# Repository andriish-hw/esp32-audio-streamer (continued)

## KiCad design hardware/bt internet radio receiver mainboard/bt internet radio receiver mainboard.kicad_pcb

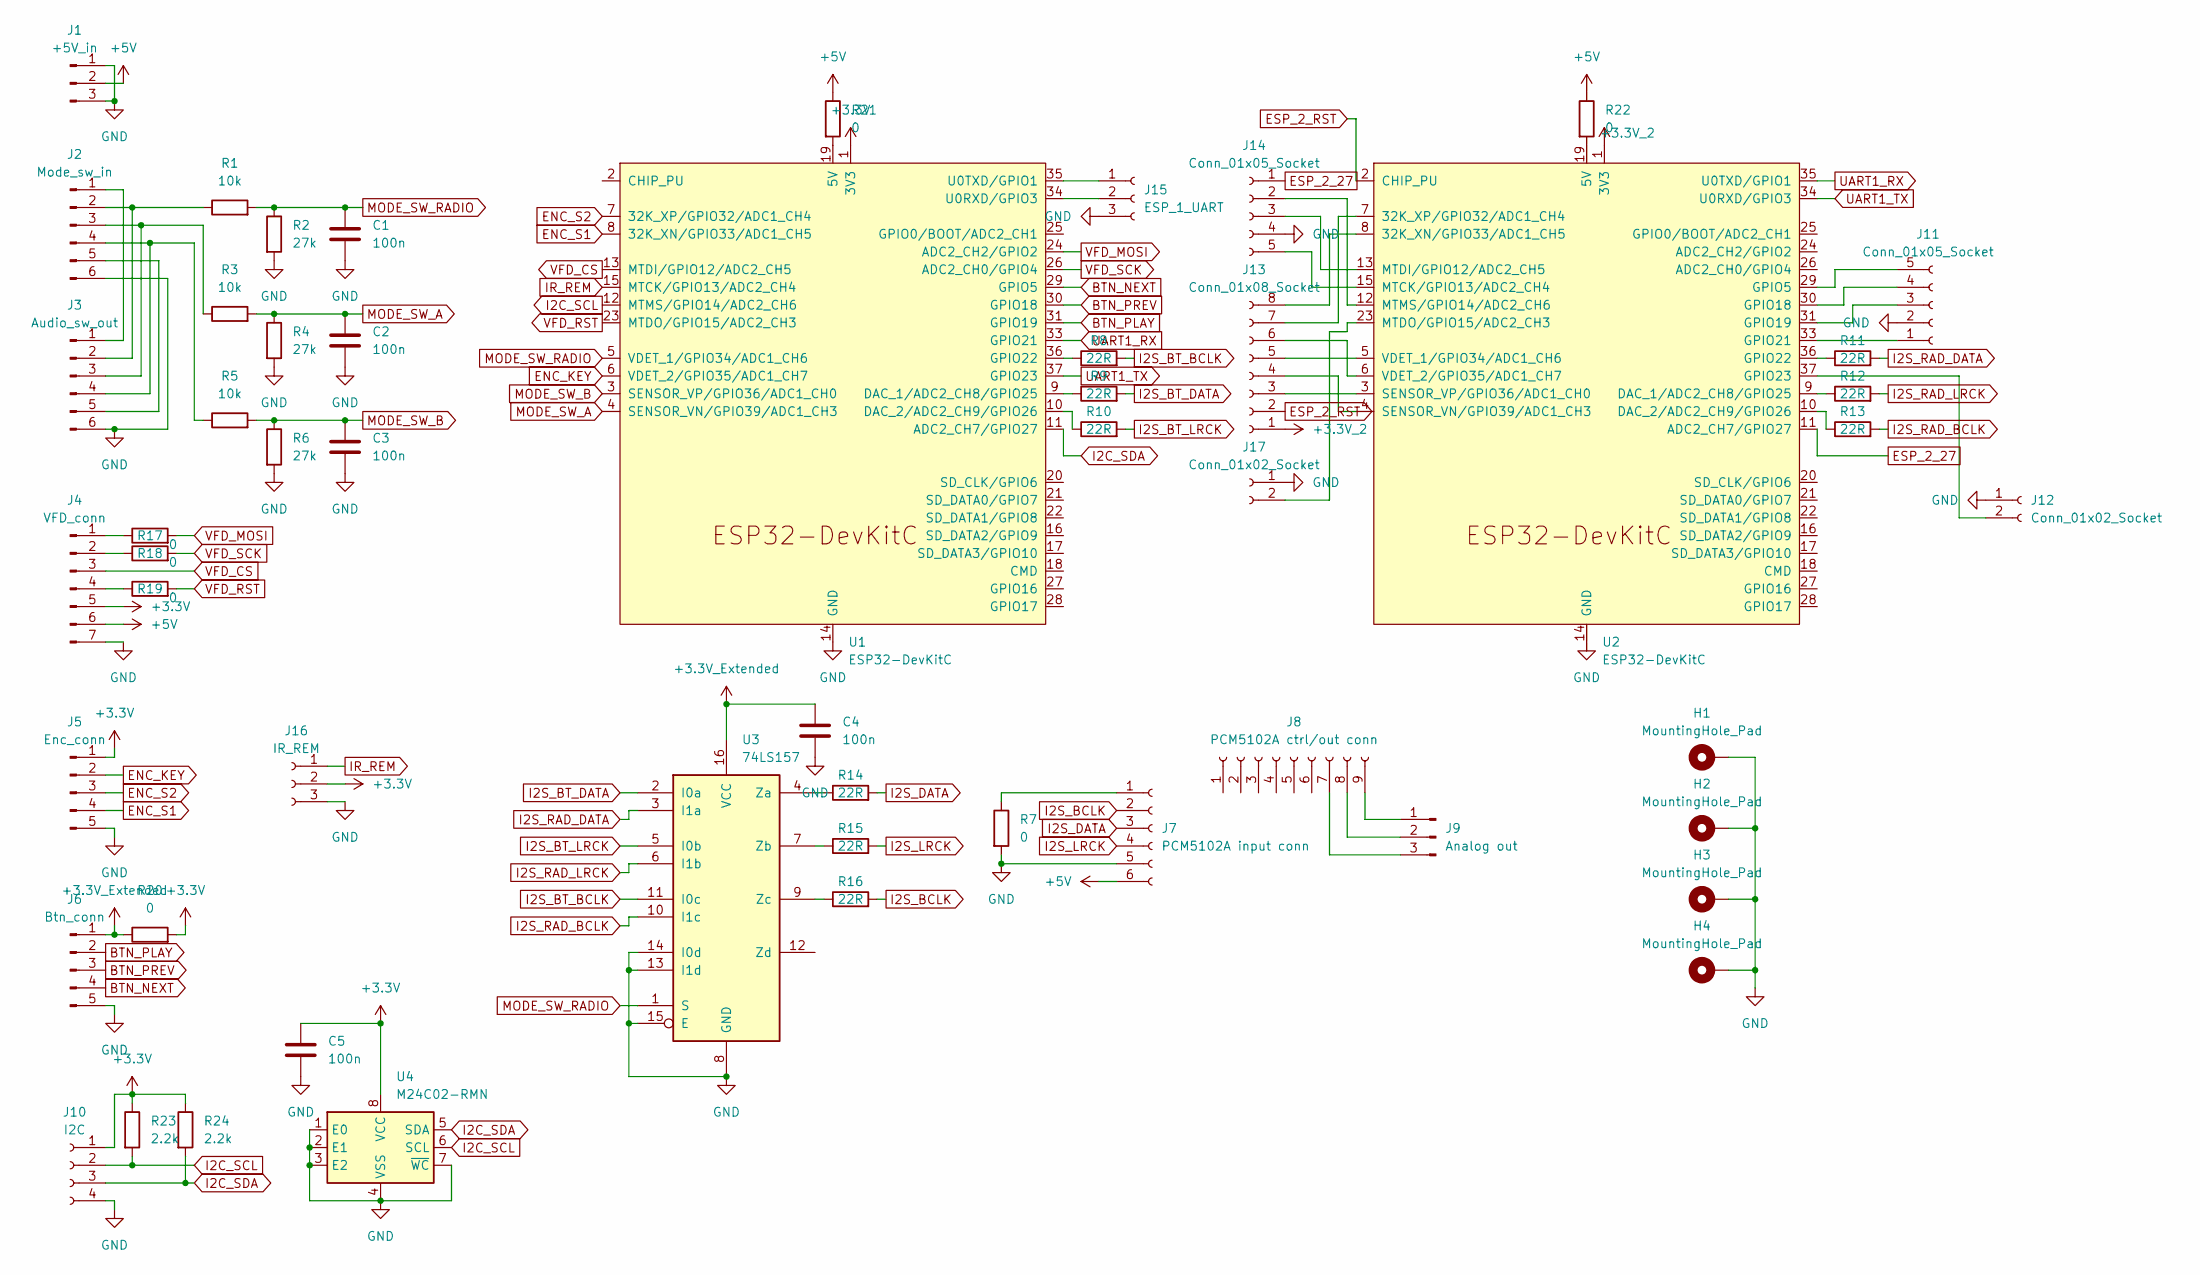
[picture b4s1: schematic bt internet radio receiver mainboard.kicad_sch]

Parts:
C1, C2, C3: 100n; C_Disc_D7.5mm_W5.0mm_P10.00mm
C4, C5: 100n; C_1206_3216Metric_Pad1.33x1.80mm_HandSolder
H1, H2, H3, H4: MountingHole_Pad; MountingHole_3.2mm_M3_DIN965_Pad_TopOnly
J1: +5V_in; PinHeader_1x03_P2.54mm_Vertical
J2: Mode_sw_in; PinHeader_1x06_P2.54mm_Vertical
J3: Audio_sw_out; PinHeader_1x06_P2.54mm_Vertical
J4: VFD_conn; PinHeader_1x07_P2.54mm_Vertical
J5: Enc_conn; PinHeader_1x05_P2.54mm_Vertical
J6: Btn_conn; PinHeader_1x05_P2.54mm_Vertical
J7: PCM5102A input conn; PinSocket_1x06_P2.54mm_Vertical
J8: PCM5102A ctrl/out conn; PinSocket_1x09_P2.54mm_Vertical
J9: Analog out; PinHeader_1x03_P2.54mm_Vertical
J10: I2C; PinSocket_1x04_P2.54mm_Vertical
J11, J14: Conn_01x05_Socket; PinSocket_1x05_P2.54mm_Vertical
J12, J17: Conn_01x02_Socket; PinSocket_1x02_P2.54mm_Vertical
J13: Conn_01x08_Socket; PinSocket_1x08_P2.54mm_Vertical
J15: ESP_1_UART; PinSocket_1x03_P2.54mm_Vertical
J16: IR_REM; PinSocket_1x03_P2.54mm_Vertical
R1, R3, R5: 10k; R_Axial_DIN0207_L6.3mm_D2.5mm_P10.16mm_Horizontal
R2, R4, R6: 27k; R_Axial_DIN0207_L6.3mm_D2.5mm_P10.16mm_Horizontal
R7, R18, R20: 0; R_Axial_DIN0207_L6.3mm_D2.5mm_P10.16mm_Horizontal
R8, R9, R10, R11, R12, R13, R14, R15, R16: 22R; R_Axial_DIN0207_L6.3mm_D2.5mm_P10.16mm_Horizontal
R17, R19: 0; R_Axial_DIN0207_L6.3mm_D2.5mm_P15.24mm_Horizontal
R21, R22: 0; R_Axial_DIN0204_L3.6mm_D1.6mm_P7.62mm_Horizontal
R23: 2.2k; R_Axial_DIN0204_L3.6mm_D1.6mm_P2.54mm_Vertical
R24: 2.2k; R_Axial_DIN0204_L3.6mm_D1.6mm_P5.08mm_Vertical
U1, U2: ESP32-DevKitC
U3: 74LS157; SOIC-16_3.9x9.9mm_P1.27mm
U4: M24C02-RMN; SOIC-8_3.9x4.9mm_P1.27mm

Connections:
+3.3V: C5.1, J4.5, J5.1, J10.1, J16.2, R20.2, R23.1, R24.1, U1.1 (3V3), U4.8 (VCC)
+3.3V_2: J13.1, U2.1 (3V3)
+3.3V_Extended: C4.1, J6.1, R20.1, U3.16 (VCC)
+5V: J1.2, J4.6, J7.6, R21.1, R22.1
BTN_NEXT: J6.4, U1.29 (GPIO5)
BTN_PLAY: J6.2, U1.31 (GPIO19)
BTN_PREV: J6.3, U1.30 (GPIO18)
ENC_KEY: J5.2, U1.6 (VDET_2/GPIO35/ADC1_CH7)
ENC_S1: J5.4, U1.8 (32K_XN/GPIO33/ADC1_CH5)
ENC_S2: J5.3, U1.7 (32K_XP/GPIO32/ADC1_CH4)
ESP_2_27: J14.1, U2.11 (ADC2_CH7/GPIO27)
ESP_2_RST: J13.2, U2.2 (CHIP_PU)
GND: C1.2, C2.2, C3.2, C4.2, C5.2, H1.1, H2.1, H3.1, H4.1, J1.1, J1.3, J2.6, J3.6, J4.7, J5.5, J6.5, J7.5, J10.4, J11.2, J12.1, J14.4, J15.3, J16.3, J17.1, R2.2, R4.2, R6.2, R7.2, U1.14 (GND), U1.32 (GND), U1.38 (GND), U2.14 (GND), U2.32 (GND), U2.38 (GND), U3.8 (GND), U3.13 (I1d), U3.14 (I0d), U3.15 (E), U4.1 (E0), U4.2 (E1), U4.3 (E2), U4.4 (VSS), U4.7 (~WC)
I2C_SCL: J10.2, R23.2, U1.12 (MTMS/GPIO14/ADC2_CH6), U4.6 (SCL)
I2C_SDA: J10.3, R24.2, U1.11 (ADC2_CH7/GPIO27), U4.5 (SDA)
I2S_BCLK: J7.2, R16.2
I2S_BT_BCLK: R8.2, U3.11 (I0c)
I2S_BT_DATA: R9.2, U3.2 (I0a)
I2S_BT_LRCK: R10.2, U3.5 (I0b)
I2S_DATA: J7.3, R14.2
I2S_LRCK: J7.4, R15.2
I2S_RAD_BCLK: R13.2, U3.10 (I1c)
I2S_RAD_DATA: R11.2, U3.3 (I1a)
I2S_RAD_LRCK: R12.2, U3.6 (I1b)
IR_REM: J16.1, U1.15 (MTCK/GPIO13/ADC2_CH4)
MODE_SW_A: C2.1, R3.2, R4.1, U1.4 (SENSOR_VN/GPIO39/ADC1_CH3)
MODE_SW_B: C3.1, R5.2, R6.1, U1.3 (SENSOR_VP/GPIO36/ADC1_CH0)
MODE_SW_RADIO: C1.1, R1.2, R2.1, U1.5 (VDET_1/GPIO34/ADC1_CH6), U3.1 (S)
unnamed: J2.1, J3.1
unnamed: J2.2, J3.2, R1.1
unnamed: J2.3, J3.3, R3.1
unnamed: J2.4, J3.4, R5.1
unnamed: J2.5, J3.5
unnamed: J4.1, R17.1
unnamed: J4.2, R18.1
unnamed: J4.4, R19.1
unnamed: J7.1, R7.1
unnamed: J8.7, J9.3
unnamed: J8.8, J9.2
unnamed: J8.9, J9.1
unnamed: J11.1, U2.33 (GPIO21)
unnamed: J11.3, U2.31 (GPIO19)
unnamed: J11.4, U2.30 (GPIO18)
unnamed: J11.5, U2.29 (GPIO5)
unnamed: J12.2, U2.37 (GPIO23)
unnamed: J13.3, U2.3 (SENSOR_VP/GPIO36/ADC1_CH0)
unnamed: J13.4, U2.4 (SENSOR_VN/GPIO39/ADC1_CH3)
unnamed: J13.5, U2.5 (VDET_1/GPIO34/ADC1_CH6)
unnamed: J13.6, U2.6 (VDET_2/GPIO35/ADC1_CH7)
unnamed: J13.7, U2.7 (32K_XP/GPIO32/ADC1_CH4)
unnamed: J13.8, U2.8 (32K_XN/GPIO33/ADC1_CH5)
unnamed: J14.2, U2.12 (MTMS/GPIO14/ADC2_CH6)
unnamed: J14.3, U2.13 (MTDI/GPIO12/ADC2_CH5)
unnamed: J14.5, U2.15 (MTCK/GPIO13/ADC2_CH4)
unnamed: J15.1, U1.35 (U0TXD/GPIO1)
unnamed: J15.2, U1.34 (U0RXD/GPIO3)
unnamed: J17.2, U2.23 (MTDO/GPIO15/ADC2_CH3)
unnamed: R21.2, U1.19 (5V)
unnamed: R9.1, U1.9 (DAC_1/ADC2_CH8/GPIO25)
unnamed: R10.1, U1.10 (DAC_2/ADC2_CH9/GPIO26)
unnamed: R8.1, U1.36 (GPIO22)
unnamed: R22.2, U2.19 (5V)
unnamed: R12.1, U2.9 (DAC_1/ADC2_CH8/GPIO25)
unnamed: R13.1, U2.10 (DAC_2/ADC2_CH9/GPIO26)
unnamed: R11.1, U2.36 (GPIO22)
unnamed: R14.1, U3.4 (Za)
unnamed: R15.1, U3.7 (Zb)
unnamed: R16.1, U3.9 (Zc)
UART1_RX: U1.33 (GPIO21), U2.35 (U0TXD/GPIO1)
UART1_TX: U1.37 (GPIO23), U2.34 (U0RXD/GPIO3)
VFD_CS: J4.3, U1.13 (MTDI/GPIO12/ADC2_CH5)
VFD_MOSI: R17.2, U1.24 (ADC2_CH2/GPIO2)
VFD_RST: R19.2, U1.23 (MTDO/GPIO15/ADC2_CH3)
VFD_SCK: R18.2, U1.26 (ADC2_CH0/GPIO4)

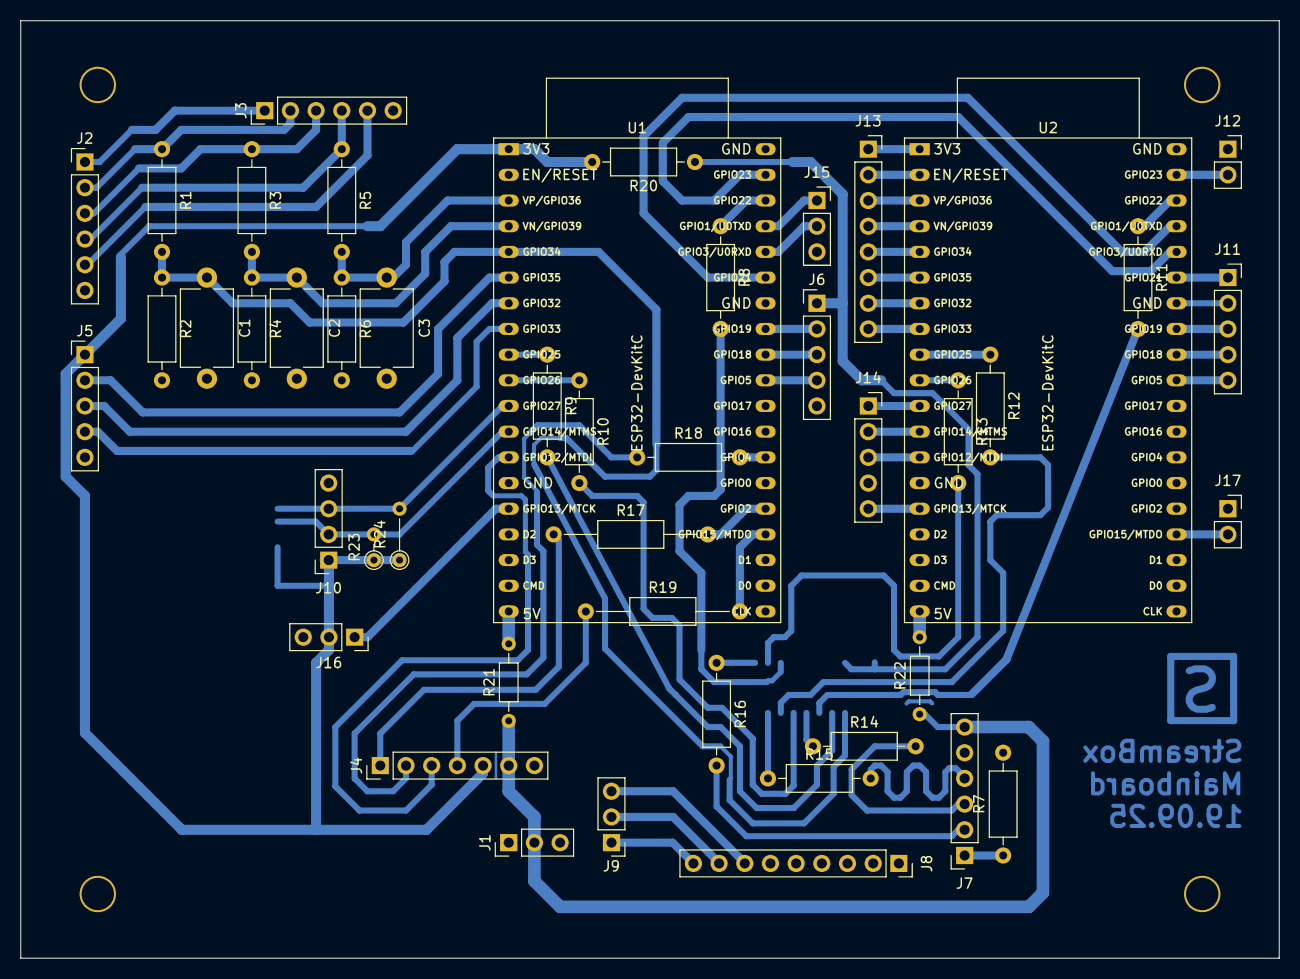
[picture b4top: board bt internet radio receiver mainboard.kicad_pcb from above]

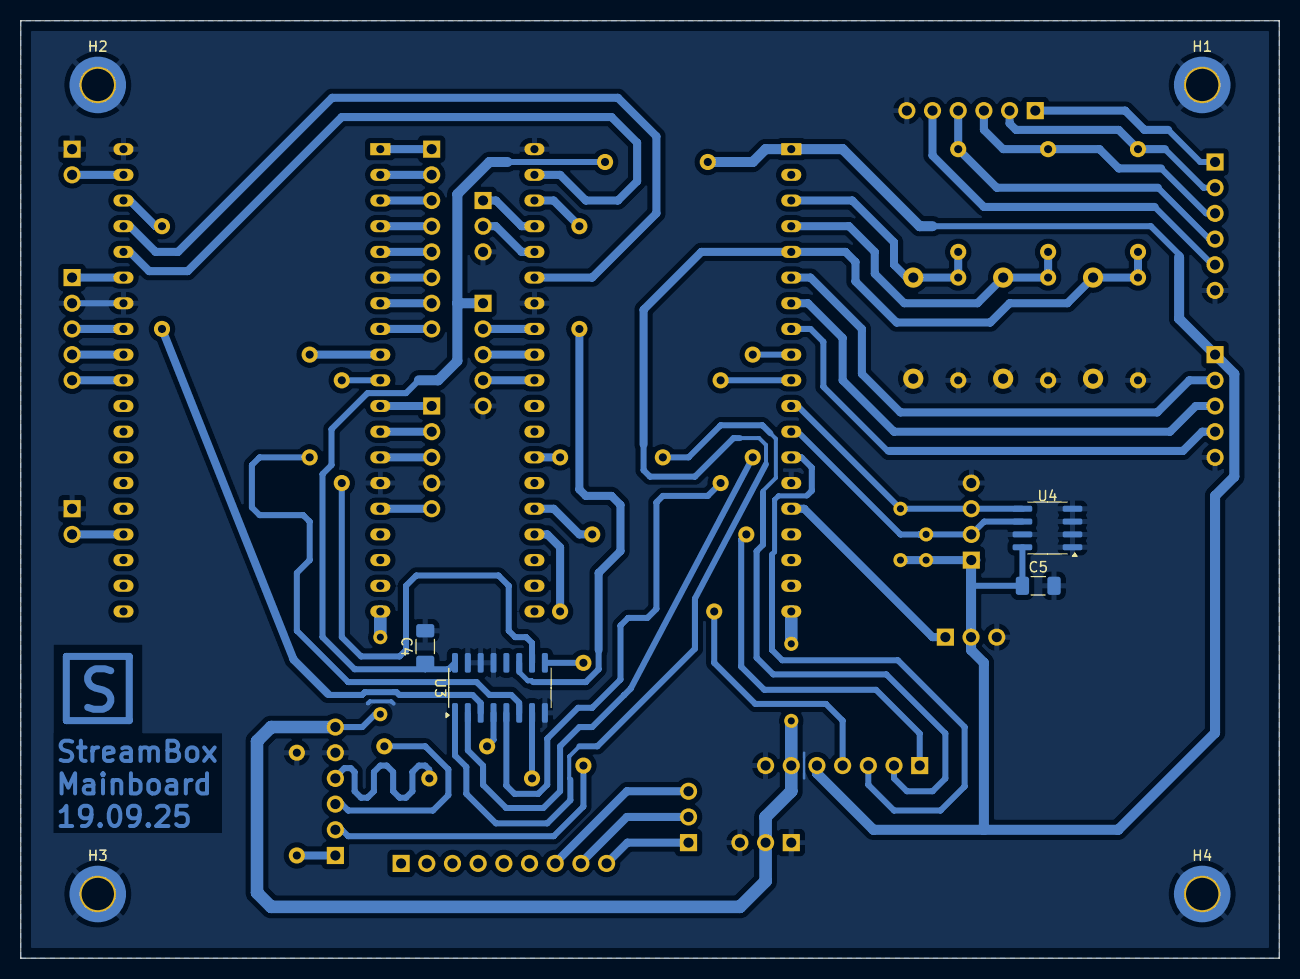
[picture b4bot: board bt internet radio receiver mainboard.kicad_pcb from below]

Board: 2 copper layers, 124.5 x 92.7 mm, 54 parts (8 on the bottom side), 74 nets.

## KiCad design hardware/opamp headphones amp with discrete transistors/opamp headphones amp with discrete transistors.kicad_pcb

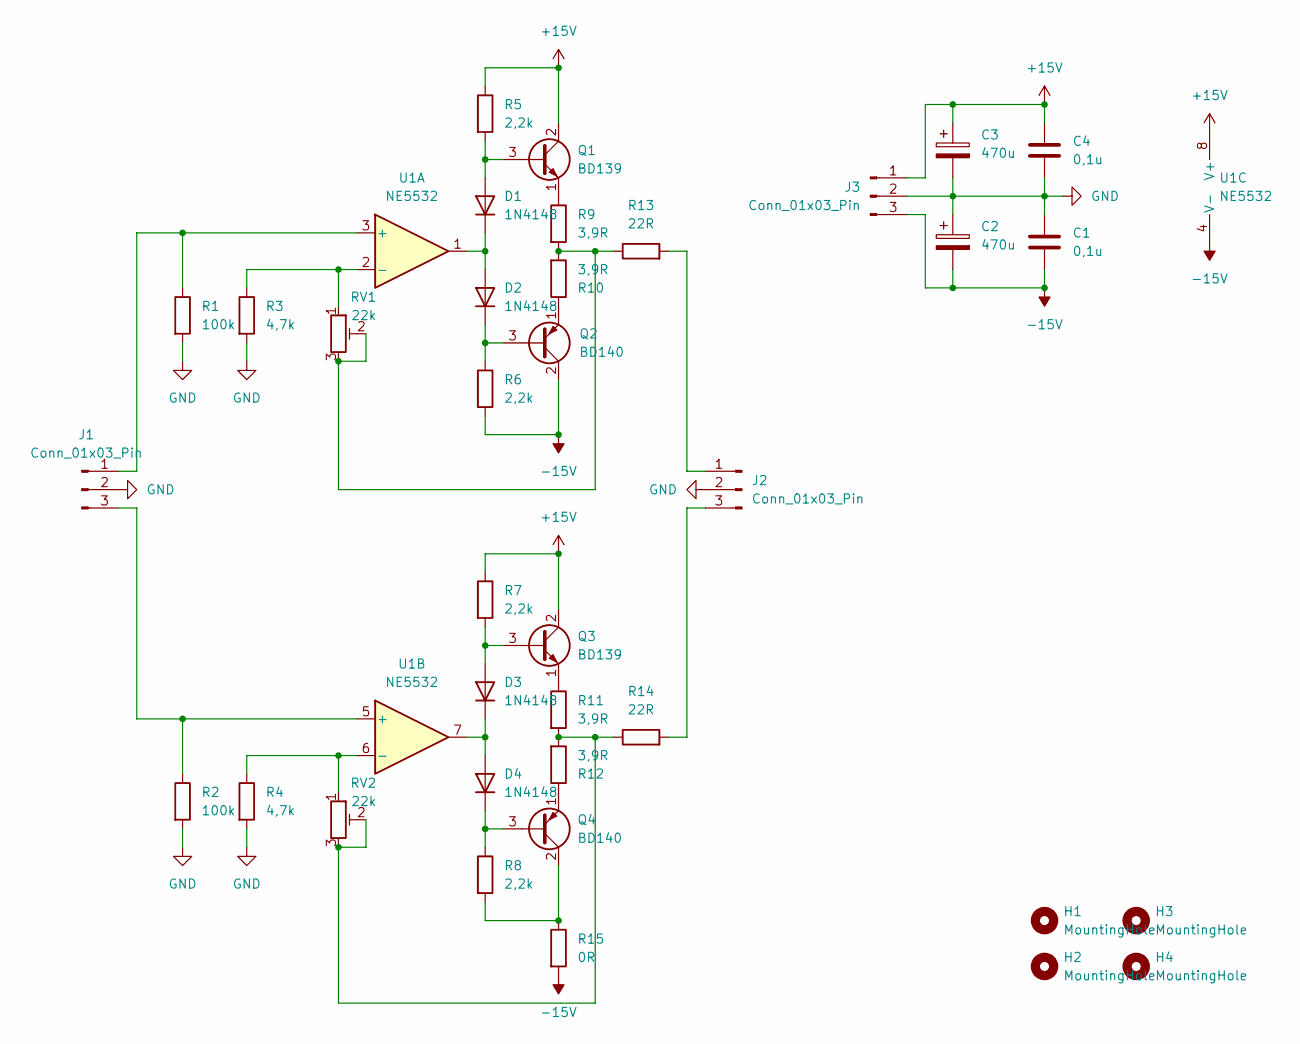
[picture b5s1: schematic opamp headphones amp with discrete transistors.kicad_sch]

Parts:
C1, C4: 0,1u; C_Disc_D5.0mm_W2.5mm_P5.00mm
C2, C3: 470u; CP_Radial_D8.0mm_P2.50mm
D1, D2, D3, D4: 1N4148; D_DO-35_SOD27_P7.62mm_Horizontal
H1, H2, H3, H4: MountingHole; MountingHole_3.2mm_M3_DIN965_Pad
J1, J2, J3: Conn_01x03_Pin; PinHeader_1x03_P2.54mm_Vertical
Q1, Q3: BD139; TO-126-3_Vertical
Q2, Q4: BD140; TO-126-3_Vertical
R1, R2: 100k; R_Axial_DIN0207_L6.3mm_D2.5mm_P10.16mm_Horizontal
R3, R4: 4,7k; R_Axial_DIN0207_L6.3mm_D2.5mm_P10.16mm_Horizontal
R5, R6, R7, R8: 2,2k; R_Axial_DIN0207_L6.3mm_D2.5mm_P10.16mm_Horizontal
R9, R10, R11, R12: 3,9R; R_Axial_DIN0309_L9.0mm_D3.2mm_P5.08mm_Vertical
R13, R14: 22R; R_Axial_DIN0309_L9.0mm_D3.2mm_P5.08mm_Vertical
R15: 0R; R_Axial_DIN0204_L3.6mm_D1.6mm_P7.62mm_Horizontal
RV1, RV2: 22k; Potentiometer_Runtron_RM-065_Vertical
U1: NE5532; DIP-8_W7.62mm_Socket_LongPads

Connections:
+15V: C3.1, C4.1, J3.1, Q1.2 (C), Q3.2 (C), R5.1, R7.1, U1.8 (V+)
-15V: C1.2, C2.2, J3.3, Q2.2 (C), R6.2, R15.2, U1.4 (V-)
GND: C1.1, C2.1, C3.2, C4.2, J1.2, J2.2, J3.2, R1.2, R2.2, R3.2, R4.2
unnamed: D1.2 (A), Q1.3 (B), R5.2
unnamed: D1.1 (K), D2.2 (A), U1.1
unnamed: D2.1 (K), Q2.3 (B), R6.1
unnamed: D3.2 (A), Q3.3 (B), R7.2
unnamed: D3.1 (K), D4.2 (A), U1.7
unnamed: D4.1 (K), Q4.3 (B), R8.1
unnamed: J1.1, R1.1, U1.3 (+)
unnamed: J1.3, R2.1, U1.5 (+)
unnamed: J2.1, R13.2
unnamed: J2.3, R14.2
unnamed: Q1.1 (E), R9.1
unnamed: Q2.1 (E), R10.1
unnamed: Q3.1 (E), R11.1
unnamed: Q4.2 (C), R8.2, R15.1
unnamed: Q4.1 (E), R12.1
unnamed: R9.2, R10.2, R13.1, RV1.2, RV1.3
unnamed: R11.2, R12.2, R14.1, RV2.2, RV2.3
unnamed: R3.1, RV1.1, U1.2 (-)
unnamed: R4.1, RV2.1, U1.6 (-)

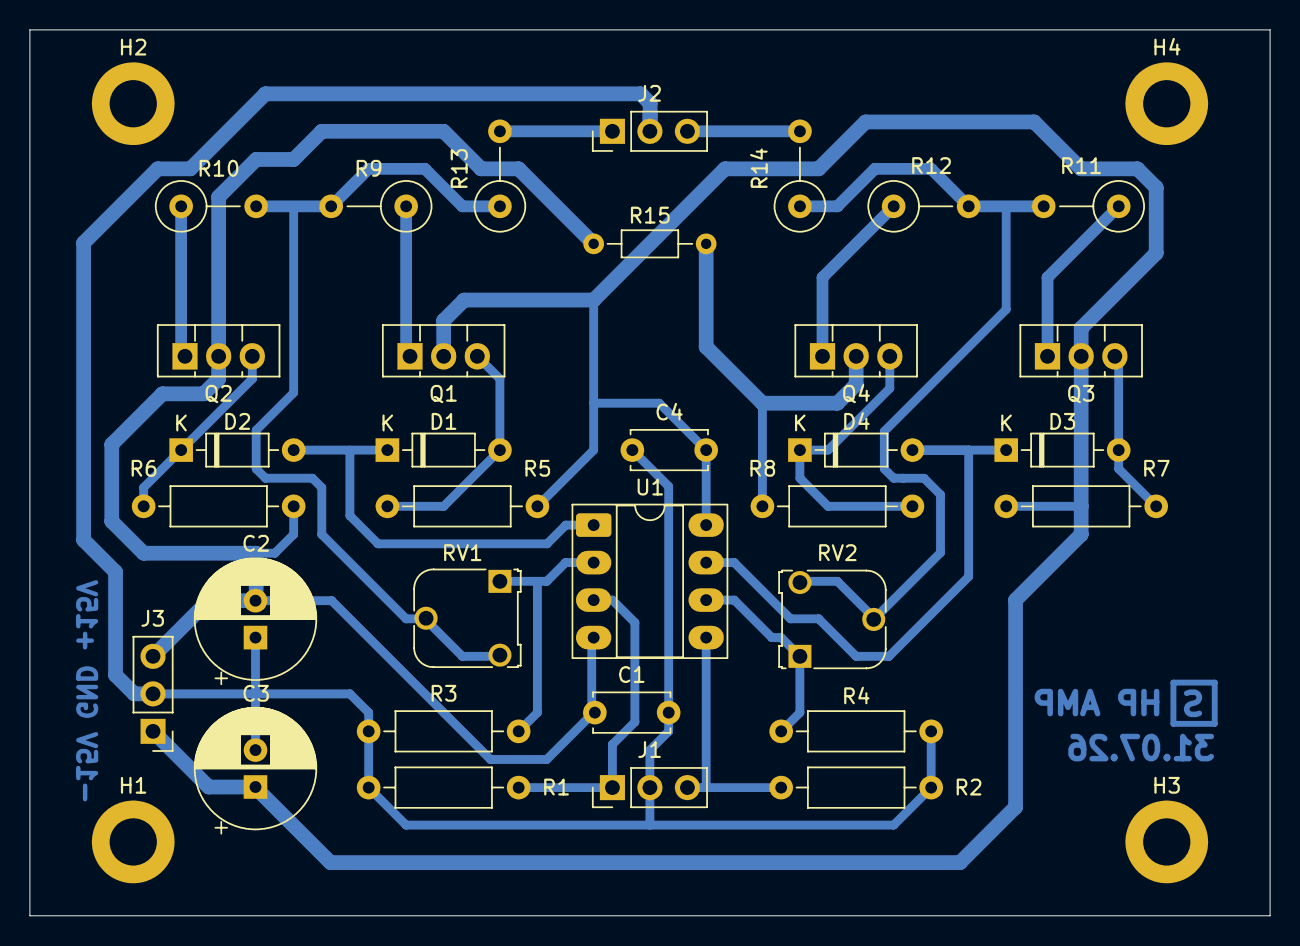
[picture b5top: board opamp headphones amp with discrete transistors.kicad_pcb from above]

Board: 2 copper layers, 84.0 x 60.0 mm, 37 parts (0 on the bottom side), 22 nets.

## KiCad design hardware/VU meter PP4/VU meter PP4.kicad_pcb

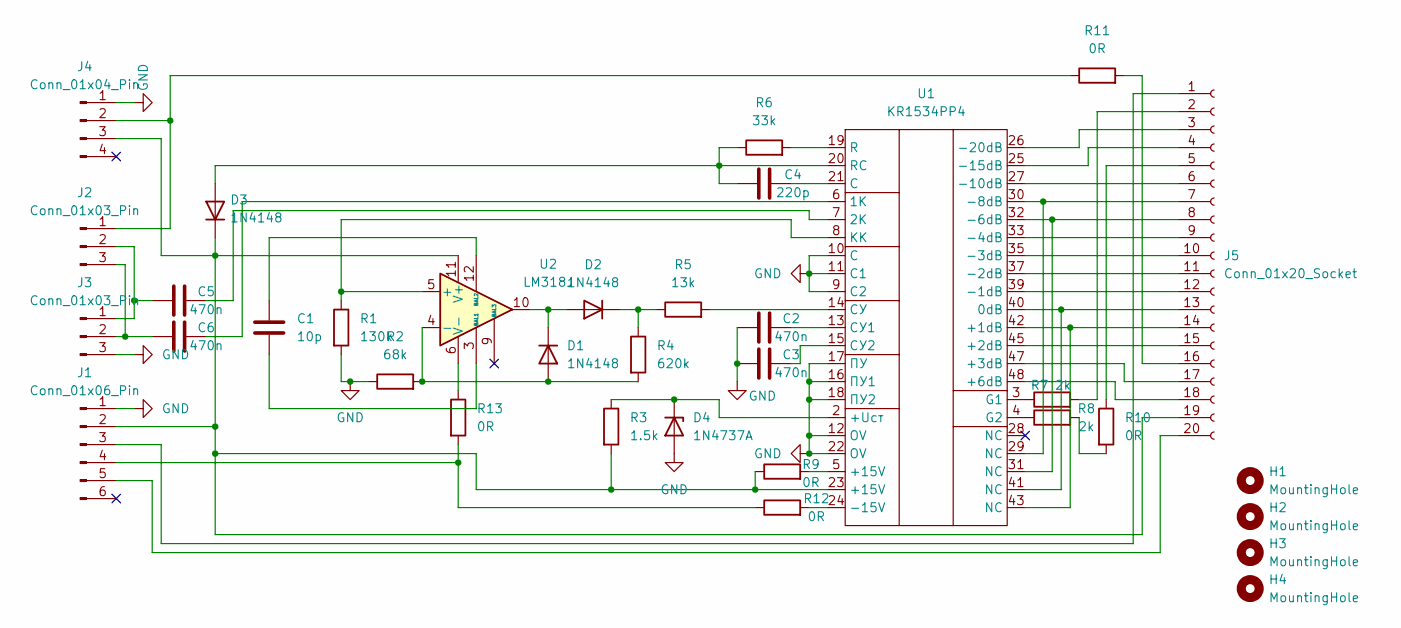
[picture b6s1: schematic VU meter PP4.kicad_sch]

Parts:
C1: 10p; C_Disc_D7.5mm_W5.0mm_P7.50mm
C2, C3, C5, C6: 470n; C_Rect_L13.0mm_W8.0mm_P10.00mm_FKS3_FKP3_MKS4
C4: 220p; C_Disc_D7.5mm_W5.0mm_P10.00mm
D1, D2: 1N4148; D_DO-35_SOD27_P7.62mm_Horizontal
D3: 1N4148; D_DO-35_SOD27_P10.16mm_Horizontal
D4: 1N4737A; D_DO-41_SOD81_P12.70mm_Horizontal
H1, H2, H3, H4: MountingHole; MountingHole_3.2mm_M3_DIN965_Pad
J1: Conn_01x06_Pin; PinHeader_1x06_P2.54mm_Vertical
J2: Conn_01x03_Pin; PinHeader_1x03_P2.54mm_Horizontal
J3: Conn_01x03_Pin; PinHeader_1x03_P2.54mm_Vertical
J4: Conn_01x04_Pin; PinHeader_1x04_P2.54mm_Vertical
J5: Conn_01x20_Socket; PinSocket_1x20_P2.54mm_Vertical
R1: 130k; R_Axial_DIN0309_L9.0mm_D3.2mm_P12.70mm_Horizontal
R2: 68k; R_Axial_DIN0309_L9.0mm_D3.2mm_P12.70mm_Horizontal
R3: 1.5k; R_Axial_DIN0309_L9.0mm_D3.2mm_P12.70mm_Horizontal
R4: 620k; R_Axial_DIN0309_L9.0mm_D3.2mm_P12.70mm_Horizontal
R5: 13k; R_Axial_DIN0309_L9.0mm_D3.2mm_P12.70mm_Horizontal
R6: 33k; R_Axial_DIN0309_L9.0mm_D3.2mm_P12.70mm_Horizontal
R7, R8: 2k; R_Axial_DIN0309_L9.0mm_D3.2mm_P12.70mm_Horizontal
R9: 0R; R_Axial_DIN0309_L9.0mm_D3.2mm_P12.70mm_Horizontal
R10, R11, R12: 0R; R_Axial_DIN0204_L3.6mm_D1.6mm_P7.62mm_Horizontal
R13: 0R; R_Axial_DIN0204_L3.6mm_D1.6mm_P5.08mm_Horizontal
U1: KR1534PP4; DIP-48_Staggered_KR1534PP4
U2: LM318J; DIP-14_W7.62mm

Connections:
GND: C2.1, C3.1, D4.2 (A), J1.1, J3.3, J4.1, R1.2, R2.1, U1.9 (С2), U1.10 (С), U1.11 (С1), U1.12 (OV), U1.16 (ПУ1), U1.17 (ПУ), U1.18 (ПУ2), U1.22 (OV)
unnamed: D1.2 (A), R2.2, R4.2, U2.4 (-)
unnamed: D1.1 (K), D2.2 (A), U2.10
unnamed: D2.1 (K), R4.1, R5.1
unnamed: C4.1, D3.2 (A), R6.1, U1.20 (RC)
unnamed: D3.1 (K), J1.2, J4.3, J5.19, R3.2, R9.1, U1.23 (+15V), U2.11 (V+)
unnamed: D4.1 (K), R3.1, U1.2 (+Uст)
unnamed: J1.3, J5.1
unnamed: J1.4, R12.1, R13.2
unnamed: J1.5, J5.20
unnamed: C5.1, J2.2, J3.1
unnamed: C6.1, J2.3, J3.2
unnamed: J2.1, J4.2, R11.1
unnamed: J5.2, R7.2
unnamed: J5.3, U1.26 (-20dB)
unnamed: J5.4, U1.25 (-15dB)
unnamed: J5.5, R10.1
unnamed: J5.6, U1.27 (-10dB)
unnamed: J5.7, U1.29 (NC), U1.30 (-8dB)
unnamed: J5.8, U1.31 (NC), U1.32 (-6dB)
unnamed: J5.9, U1.33 (-4dB)
unnamed: J5.10, U1.35 (-3dB)
unnamed: J5.11, U1.37 (-2dB)
unnamed: J5.12, U1.39 (-1dB)
unnamed: J5.13, U1.40 (0dB), U1.41 (NC)
unnamed: J5.14, U1.42 (+1dB), U1.43 (NC)
unnamed: J5.15, U1.45 (+2dB)
unnamed: J5.16, R11.2
unnamed: J5.17, U1.47 (+3dB)
unnamed: J5.18, U1.48 (+6dB)
unnamed: R9.2, U1.5 (+15V)
unnamed: R8.2, R10.2
unnamed: C6.2, U1.6 (1К)
unnamed: C5.2, U1.7 (2К)
unnamed: R12.2, U1.24 (-15V)
unnamed: C4.2, U1.21 (C)
unnamed: R7.1, U1.3 (G1)
unnamed: R8.1, U1.4 (G2)
unnamed: R6.2, U1.19 (R)
unnamed: R1.1, U1.8 (КК), U2.5 (+)
unnamed: C2.2, U1.13 (СУ1)
unnamed: C3.2, U1.15 (СУ2)
unnamed: R5.2, U1.14 (СУ)
unnamed: C1.1, U2.3 (BAL1)
unnamed: C1.2, U2.12 (BAL2)
unnamed: R13.1, U2.6 (V-)

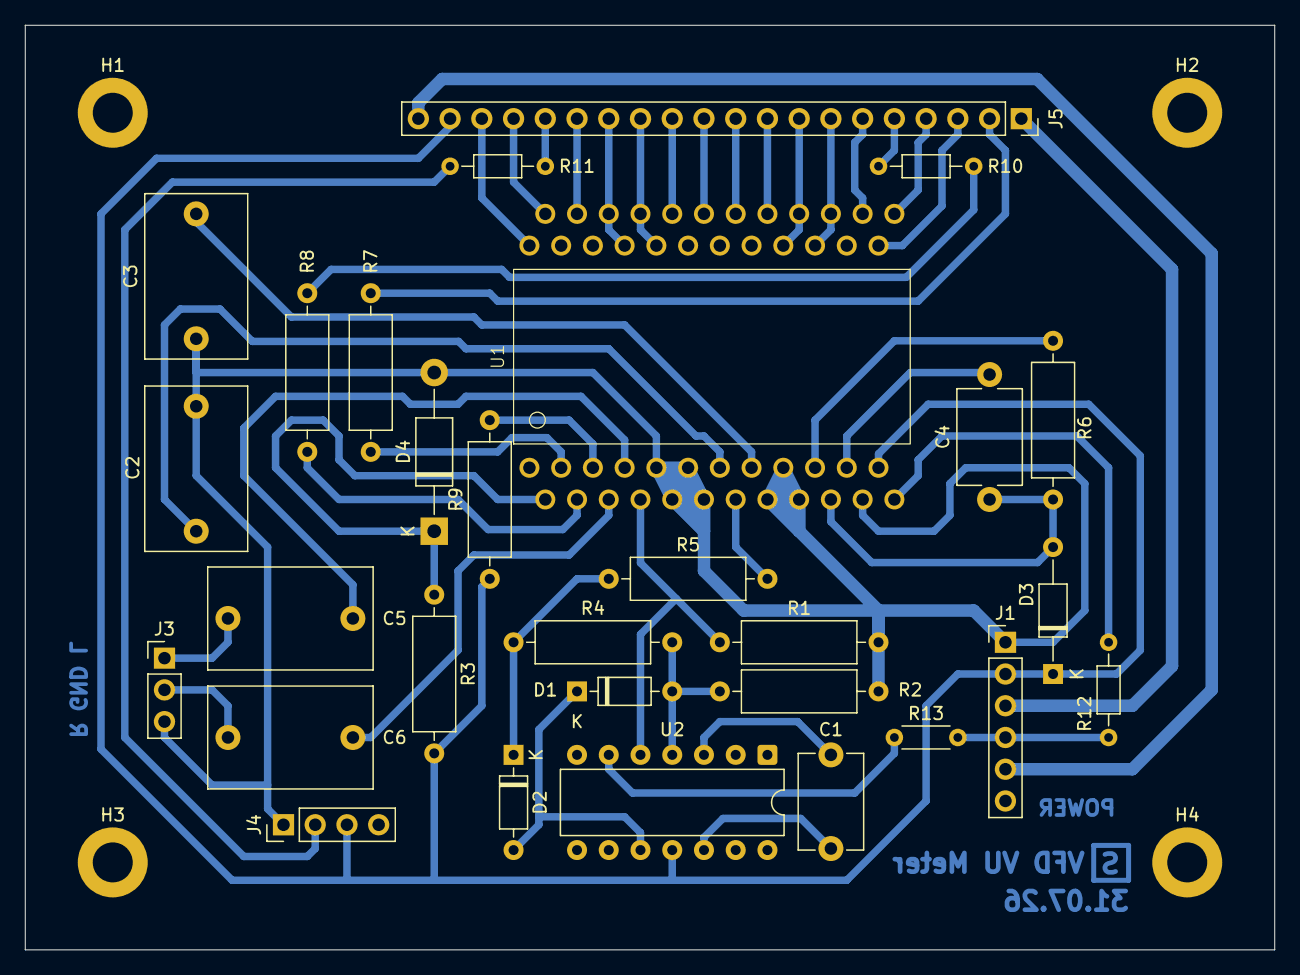
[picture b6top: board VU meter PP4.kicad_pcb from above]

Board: 2 copper layers, 100.0 x 74.0 mm, 33 parts (0 on the bottom side), 46 nets.

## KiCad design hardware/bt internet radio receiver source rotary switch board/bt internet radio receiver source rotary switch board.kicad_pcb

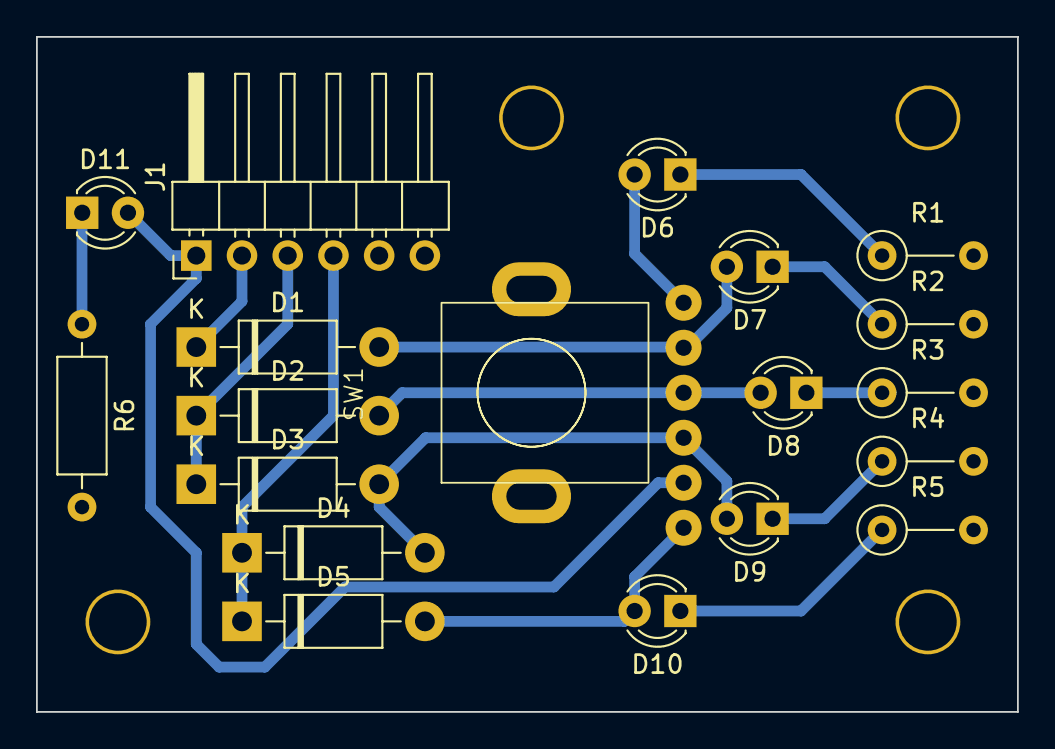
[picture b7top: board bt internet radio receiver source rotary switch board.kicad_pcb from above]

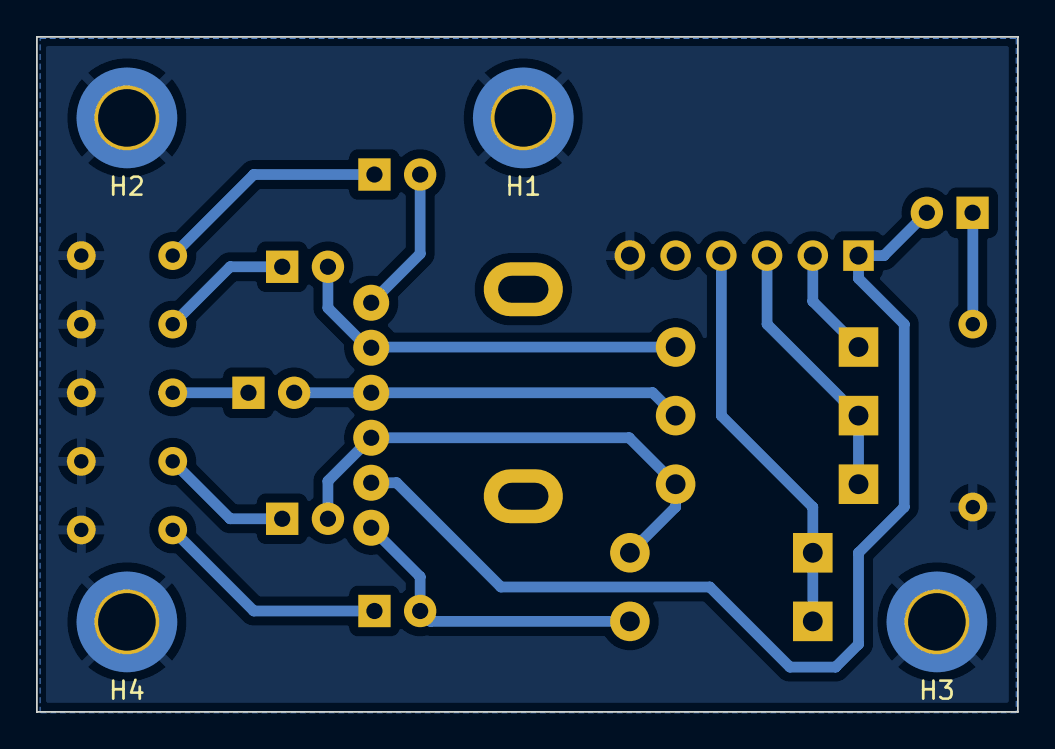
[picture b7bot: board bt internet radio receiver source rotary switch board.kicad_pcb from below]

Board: 2 copper layers, 54.5 x 37.5 mm, 23 parts (4 on the bottom side), 16 nets.

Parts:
D1, D2, D3, D4, D5: 1N5819; D_DO-41_SOD81_P10.16mm_Horizontal
D6, D7, D8, D9, D10, D11: LED; LED_D3.0mm_FlatTop
H1, H2, H3, H4: MountingHole_Pad; MountingHole_3.2mm_M3_DIN965_Pad_TopOnly
J1: Conn_01x06_Pin; PinHeader_1x06_P2.54mm_Horizontal
R1, R2, R3, R4, R5: 330R; R_Axial_DIN0207_L6.3mm_D2.5mm_P5.08mm_Vertical
R6: 330R; R_Axial_DIN0207_L6.3mm_D2.5mm_P10.16mm_Horizontal
SW1: RS1010_1P5T; RS1010_custom_vertical

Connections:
GND: H1.1, H2.1, H3.1, H4.1, J1.6, R1.2, R2.2, R3.2, R4.2, R5.2, R6.2
unnamed: D1.2 (A), D7.2 (A), SW1.2
unnamed: D1.1 (K), J1.2
unnamed: D2.2 (A), D8.2 (A), SW1.3
unnamed: D2.1 (K), D3.1 (K), J1.3
unnamed: D3.2 (A), D4.2 (A), D9.2 (A), SW1.4
unnamed: D4.1 (K), D5.1 (K), J1.4
unnamed: D6.2 (A), SW1.1
unnamed: D6.1 (K), R1.1
unnamed: D7.1 (K), R2.1
unnamed: D8.1 (K), R3.1
unnamed: D9.1 (K), R4.1
unnamed: D5.2 (A), D10.2 (A), SW1.10
unnamed: D10.1 (K), R5.1
unnamed: D11.2 (A), J1.1, SW1.5
unnamed: D11.1 (K), R6.1

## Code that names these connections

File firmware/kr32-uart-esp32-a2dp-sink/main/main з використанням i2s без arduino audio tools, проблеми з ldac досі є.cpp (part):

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#define ENC_B GPIO_NUM_32

// Buttons
#define BTN_PLAY GPIO_NUM_19
#define BTN_PREV GPIO_NUM_18
#define BTN_NEXT GPIO_NUM_5
#define BTN_ENC GPIO_NUM_35

// Rotary switch
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    gpio_config(&io_conf);

    gpio_config_t io_conf_b = {
        .pin_bit_mask = (1ULL << BTN_PLAY) | (1ULL << BTN_PREV) | (1ULL << BTN_NEXT),
        .mode = GPIO_MODE_INPUT,
        .pull_up_en = GPIO_PULLUP_ENABLE,
        .pull_down_en = GPIO_PULLDOWN_DISABLE,
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    gpio_isr_handler_add(ROT_SW_A,      rot_sw_handler, (void*) ROT_SW_A);
    gpio_isr_handler_add(ROT_SW_B,      rot_sw_handler, (void*) ROT_SW_B);
    gpio_isr_handler_add(ENC_A, encoder_isr_handler, NULL);
	//gpio_set_direction(BTN_PLAY, GPIO_MODE_INPUT);
}

bool enc_isLeft(void) {
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			ESP_LOGW("ENC", "Direction changed");
			dir_changed = false;
		}*/
        //bool pressed = (gpio_get_level(BTN_PLAY) == 0);
        TickType_t now = xTaskGetTickCount();
		uint32_t now_ms = now * portTICK_PERIOD_MS;

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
